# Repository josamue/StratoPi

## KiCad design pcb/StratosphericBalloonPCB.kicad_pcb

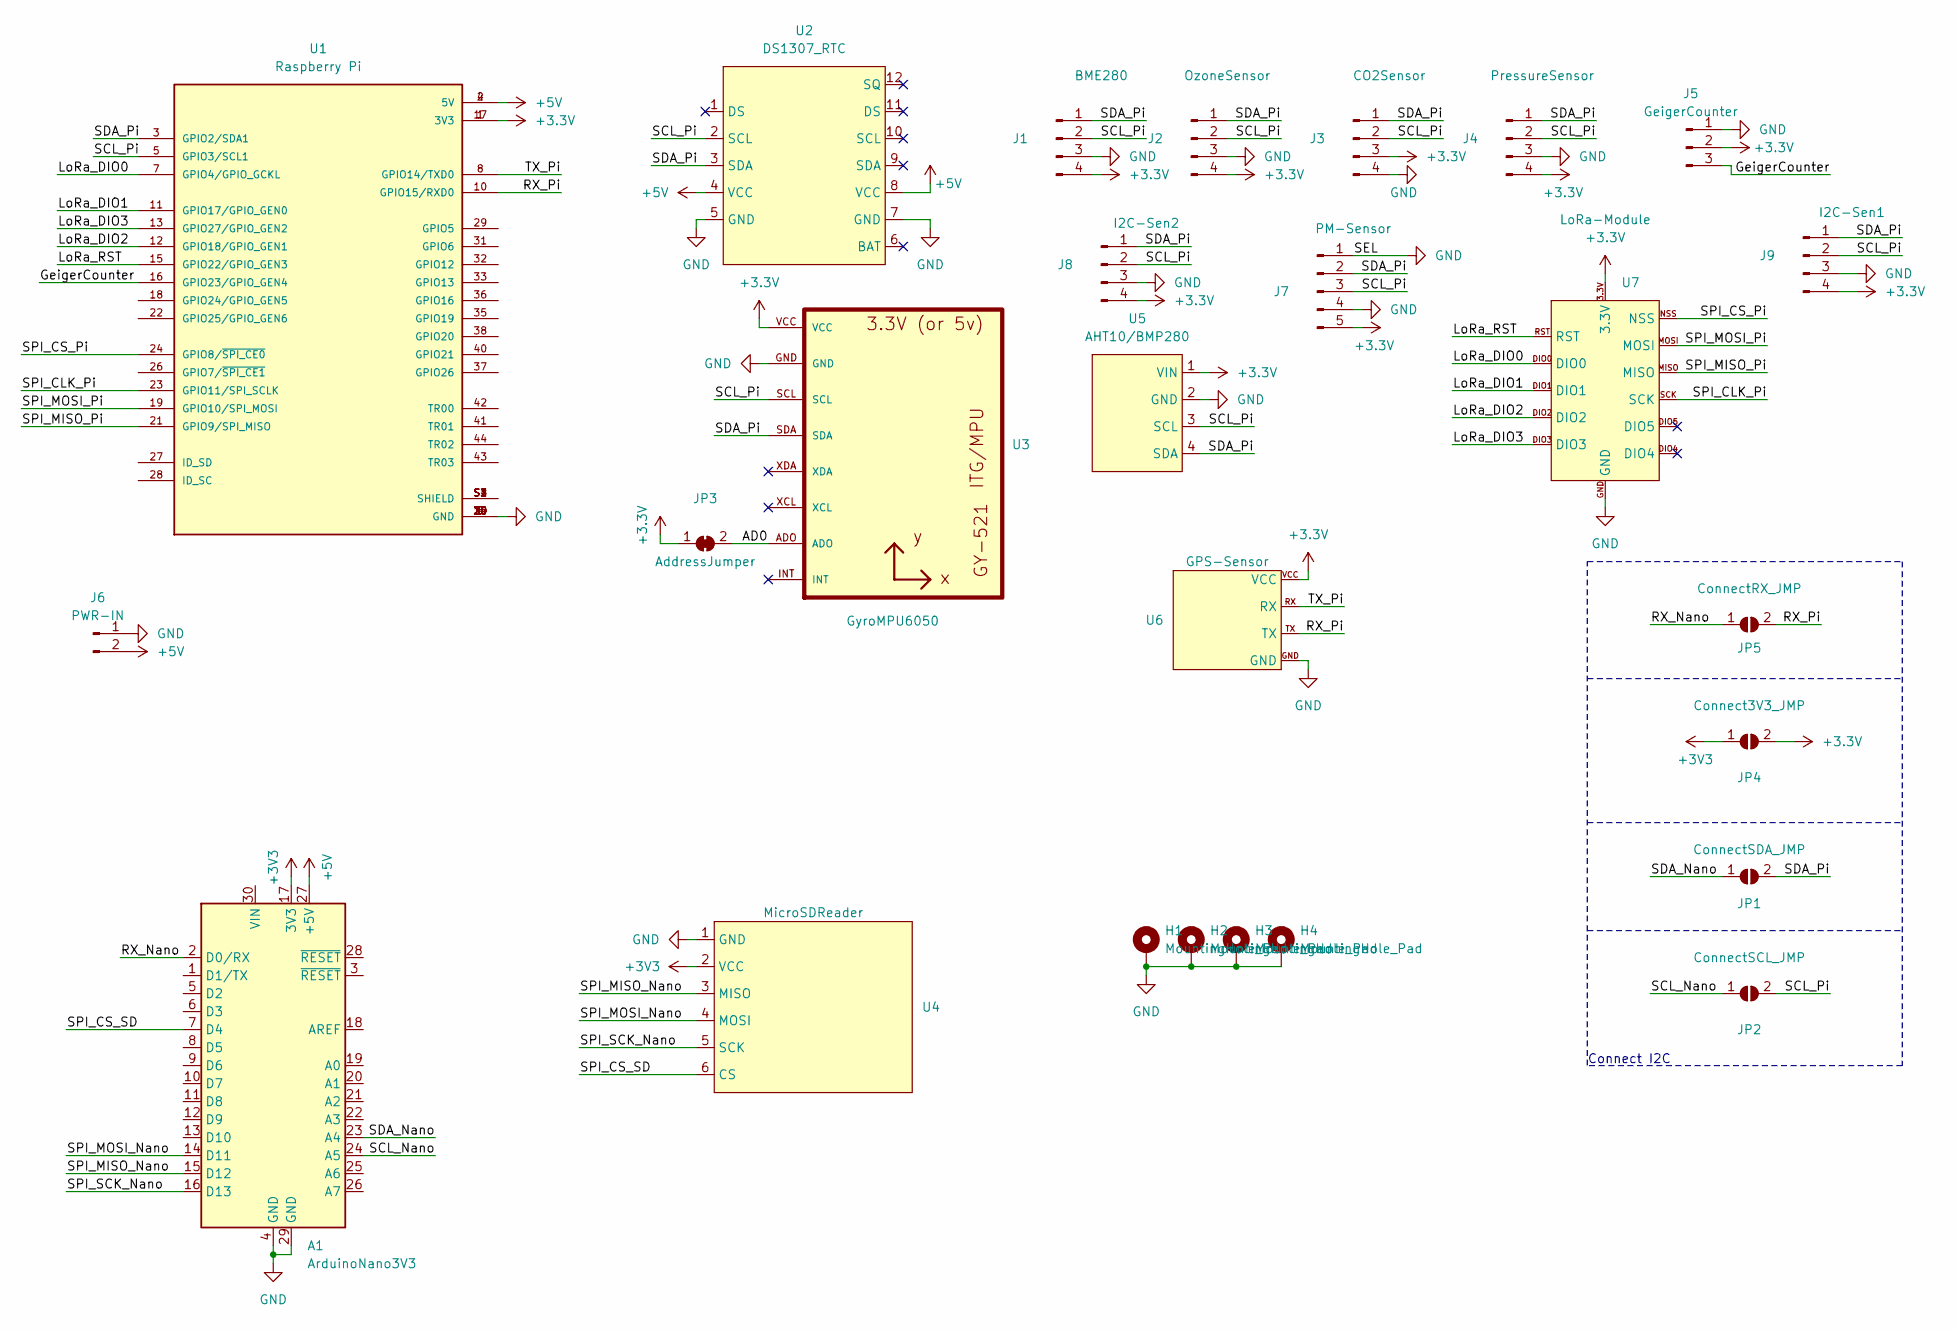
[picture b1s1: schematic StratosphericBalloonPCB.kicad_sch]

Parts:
A1: ArduinoNano3V3; Arduino_Nano
H1, H2, H3, H4: MountingHole_Pad; MountingHole_2.2mm_M2_DIN965_Pad
J1: BME280; JST_XH_B4B-XH-A_1x04_P2.50mm_Vertical
J2: OzoneSensor; JST_XH_B4B-XH-A_1x04_P2.50mm_Vertical
J3: CO2Sensor; JST_XH_B4B-XH-A_1x04_P2.50mm_Vertical
J4: PressureSensor; JST_XH_B4B-XH-A_1x04_P2.50mm_Vertical
J5: GeigerCounter; JST_XH_B3B-XH-A_1x03_P2.50mm_Vertical
J6: PWR-IN; JST_XH_B2B-XH-A_1x02_P2.50mm_Vertical
J7: PM-Sensor; JST_XH_B5B-XH-A_1x05_P2.50mm_Vertical
J8: I2C-Sen2; JST_XH_B4B-XH-A_1x04_P2.50mm_Vertical
J9: I2C-Sen1; JST_XH_B4B-XH-A_1x04_P2.50mm_Vertical
JP1: ConnectSDA_JMP; SolderJumper-2_P1.3mm_Open_Pad1.0x1.5mm
JP2: ConnectSCL_JMP; SolderJumper-2_P1.3mm_Open_Pad1.0x1.5mm
JP3: AddressJumper; SolderJumper-2_P1.3mm_Bridged_Pad1.0x1.5mm
JP4: Connect3V3_JMP; SolderJumper-2_P1.3mm_Open_Pad1.0x1.5mm
JP5: ConnectRX_JMP; SolderJumper-2_P1.3mm_Open_Pad1.0x1.5mm
U1: Raspberry Pi; RaspberryPi4b; PARTREV 4
U2: DS1307_RTC; DS1307 Module
U3: GyroMPU6050; GY-521_1
U4: MicroSDReader
U5: AHT10/BMP280; AHT10Breakout
U6: GPS-Sensor; NEOM8N-Breakout
U7: LoRa-Module; SX1278_LoRa

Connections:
+3.3V: J1.4, J2.4, J3.3, J4.4, J5.2, J7.5, J8.4, J9.4, JP3.1 (A), JP4.2 (B), U1.1 (3V3), U1.17 (3V3), U3.VCC, U5.1 (VIN), U6.VCC, U7.3.3V
+3V3: A1.17 (3V3), JP4.1 (A), U4.2 (VCC)
+5V: A1.27 (+5V), J6.2, U1.2 (5V), U1.4 (5V), U2.4 (VCC), U2.8 (VCC)
/AD0: JP3.2 (B), U3.ADO
/GeigerCounter: J5.3, U1.16 (GPIO23/GPIO_GEN4)
/LoRa_DIO0: U1.7 (GPIO4/GPIO_GCKL), U7.DIO0
/LoRa_DIO1: U1.11 (GPIO17/GPIO_GEN0), U7.DIO1
/LoRa_DIO2: U1.12 (GPIO18/GPIO_GEN1), U7.DIO2
/LoRa_DIO3: U1.13 (GPIO27/GPIO_GEN2), U7.DIO3
/LoRa_RST: U1.15 (GPIO22/GPIO_GEN3), U7.RST
/RX_Nano: A1.2 (D0/RX), JP5.1 (A)
/RX_Pi: JP5.2 (B), U1.10 (GPIO15/RXD0), U6.TX
/SCL_Nano: A1.24 (A5), JP2.1 (A)
/SCL_Pi: J1.2, J2.2, J3.2, J4.2, J7.3, J8.2, J9.2, JP2.2 (B), U1.5 (GPIO3/SCL1), U2.2 (SCL), U3.SCL, U5.3 (SCL)
/SDA_Nano: A1.23 (A4), JP1.1 (A)
/SDA_Pi: J1.1, J2.1, J3.1, J4.1, J7.2, J8.1, J9.1, JP1.2 (B), U1.3 (GPIO2/SDA1), U2.3 (SDA), U3.SDA, U5.4 (SDA)
/SPI_CLK_Pi: U1.23 (GPIO11/SPI_SCLK), U7.SCK
/SPI_CS_Pi: U1.24 (GPIO8/~SPI_CE0), U7.NSS
/SPI_CS_SD: A1.7 (D4), U4.6 (CS)
/SPI_MISO_Nano: A1.15 (D12), U4.3 (MISO)
/SPI_MISO_Pi: U1.21 (GPIO9/SPI_MISO), U7.MISO
/SPI_MOSI_Nano: A1.14 (D11), U4.4 (MOSI)
/SPI_MOSI_Pi: U1.19 (GPIO10/SPI_MOSI), U7.MOSI
/SPI_SCK_Nano: A1.16 (D13), U4.5 (SCK)
/TX_Pi: U1.8 (GPIO14/TXD0), U6.RX
GND: A1.4 (GND), A1.29 (GND), H1.1, H2.1, H3.1, H4.1, J1.3, J2.3, J3.4, J4.3, J5.1, J6.1, J7.1, J7.4, J8.3, J9.3, U1.6 (GND), U1.9 (GND), U1.14 (GND), U1.20 (GND), U1.25 (GND), U1.30 (GND), U1.34 (GND), U1.39 (GND), U2.5 (GND), U2.7 (GND), U3.GND, U4.1 (GND), U5.2 (GND), U6.GND, U7.GND
unnamed: U1.S1 (SHIELD), U1.S2 (SHIELD), U1.S3 (SHIELD), U1.S4 (SHIELD)

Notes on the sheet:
Connect I2C

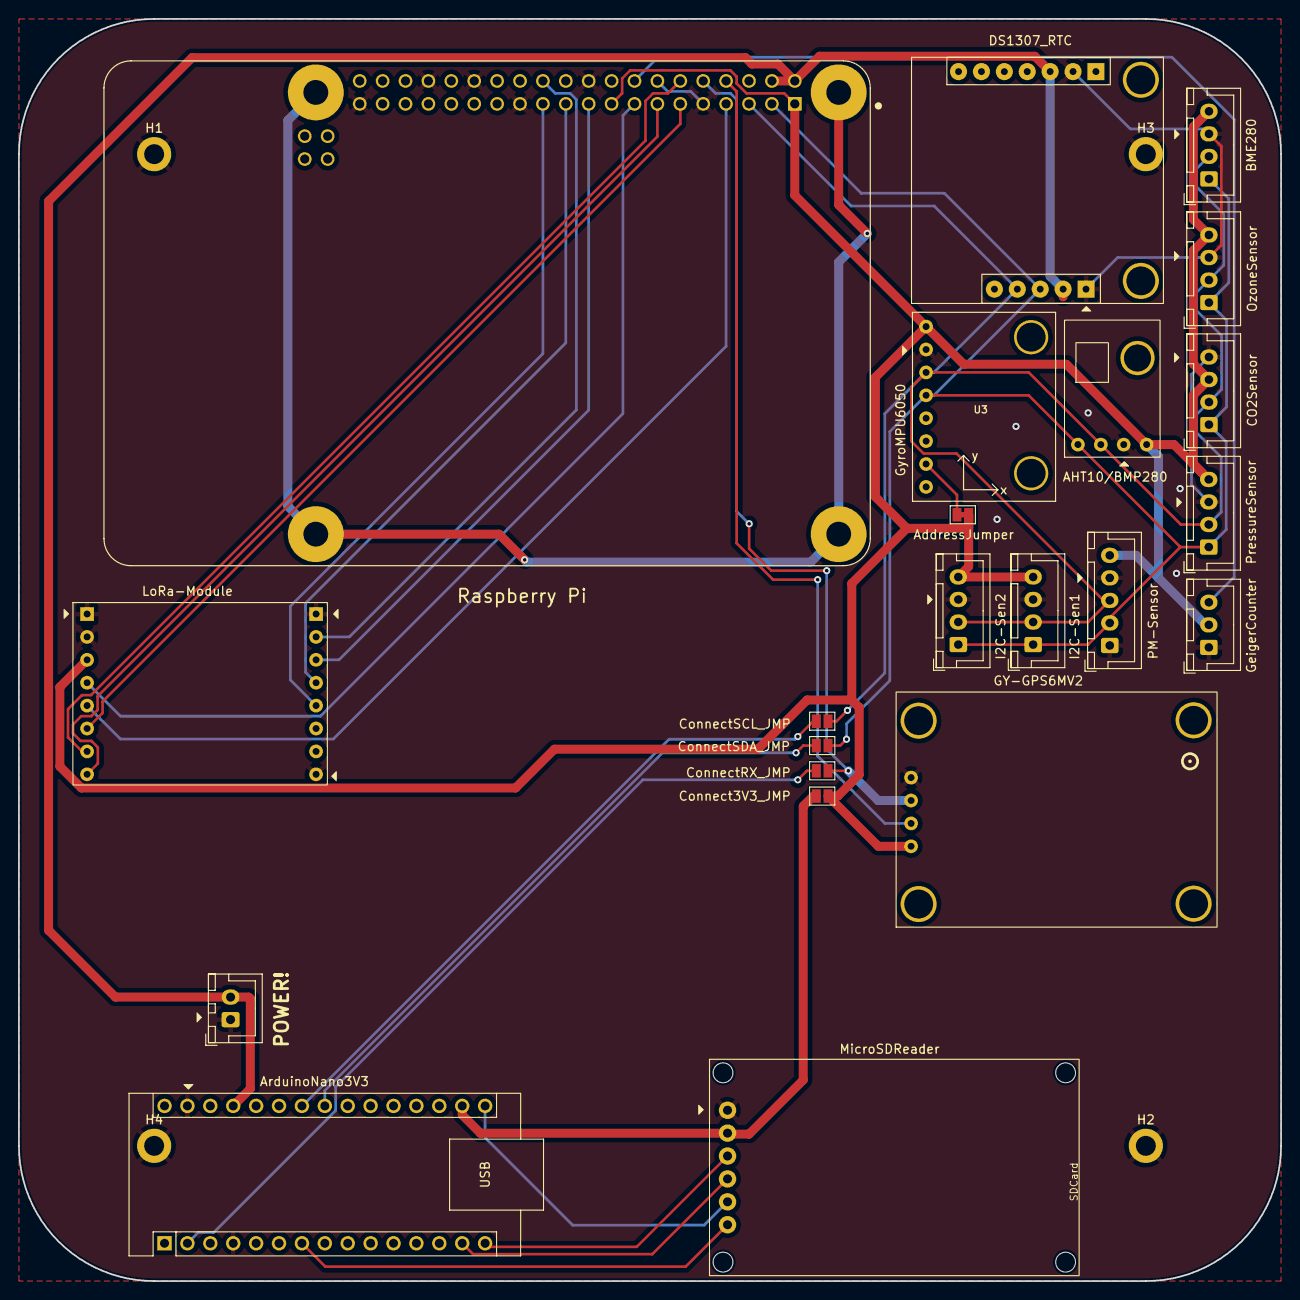
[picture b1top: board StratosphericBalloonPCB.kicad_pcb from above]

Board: 2 copper layers, 140.0 x 140.0 mm, 26 parts (0 on the bottom side), 27 nets.
